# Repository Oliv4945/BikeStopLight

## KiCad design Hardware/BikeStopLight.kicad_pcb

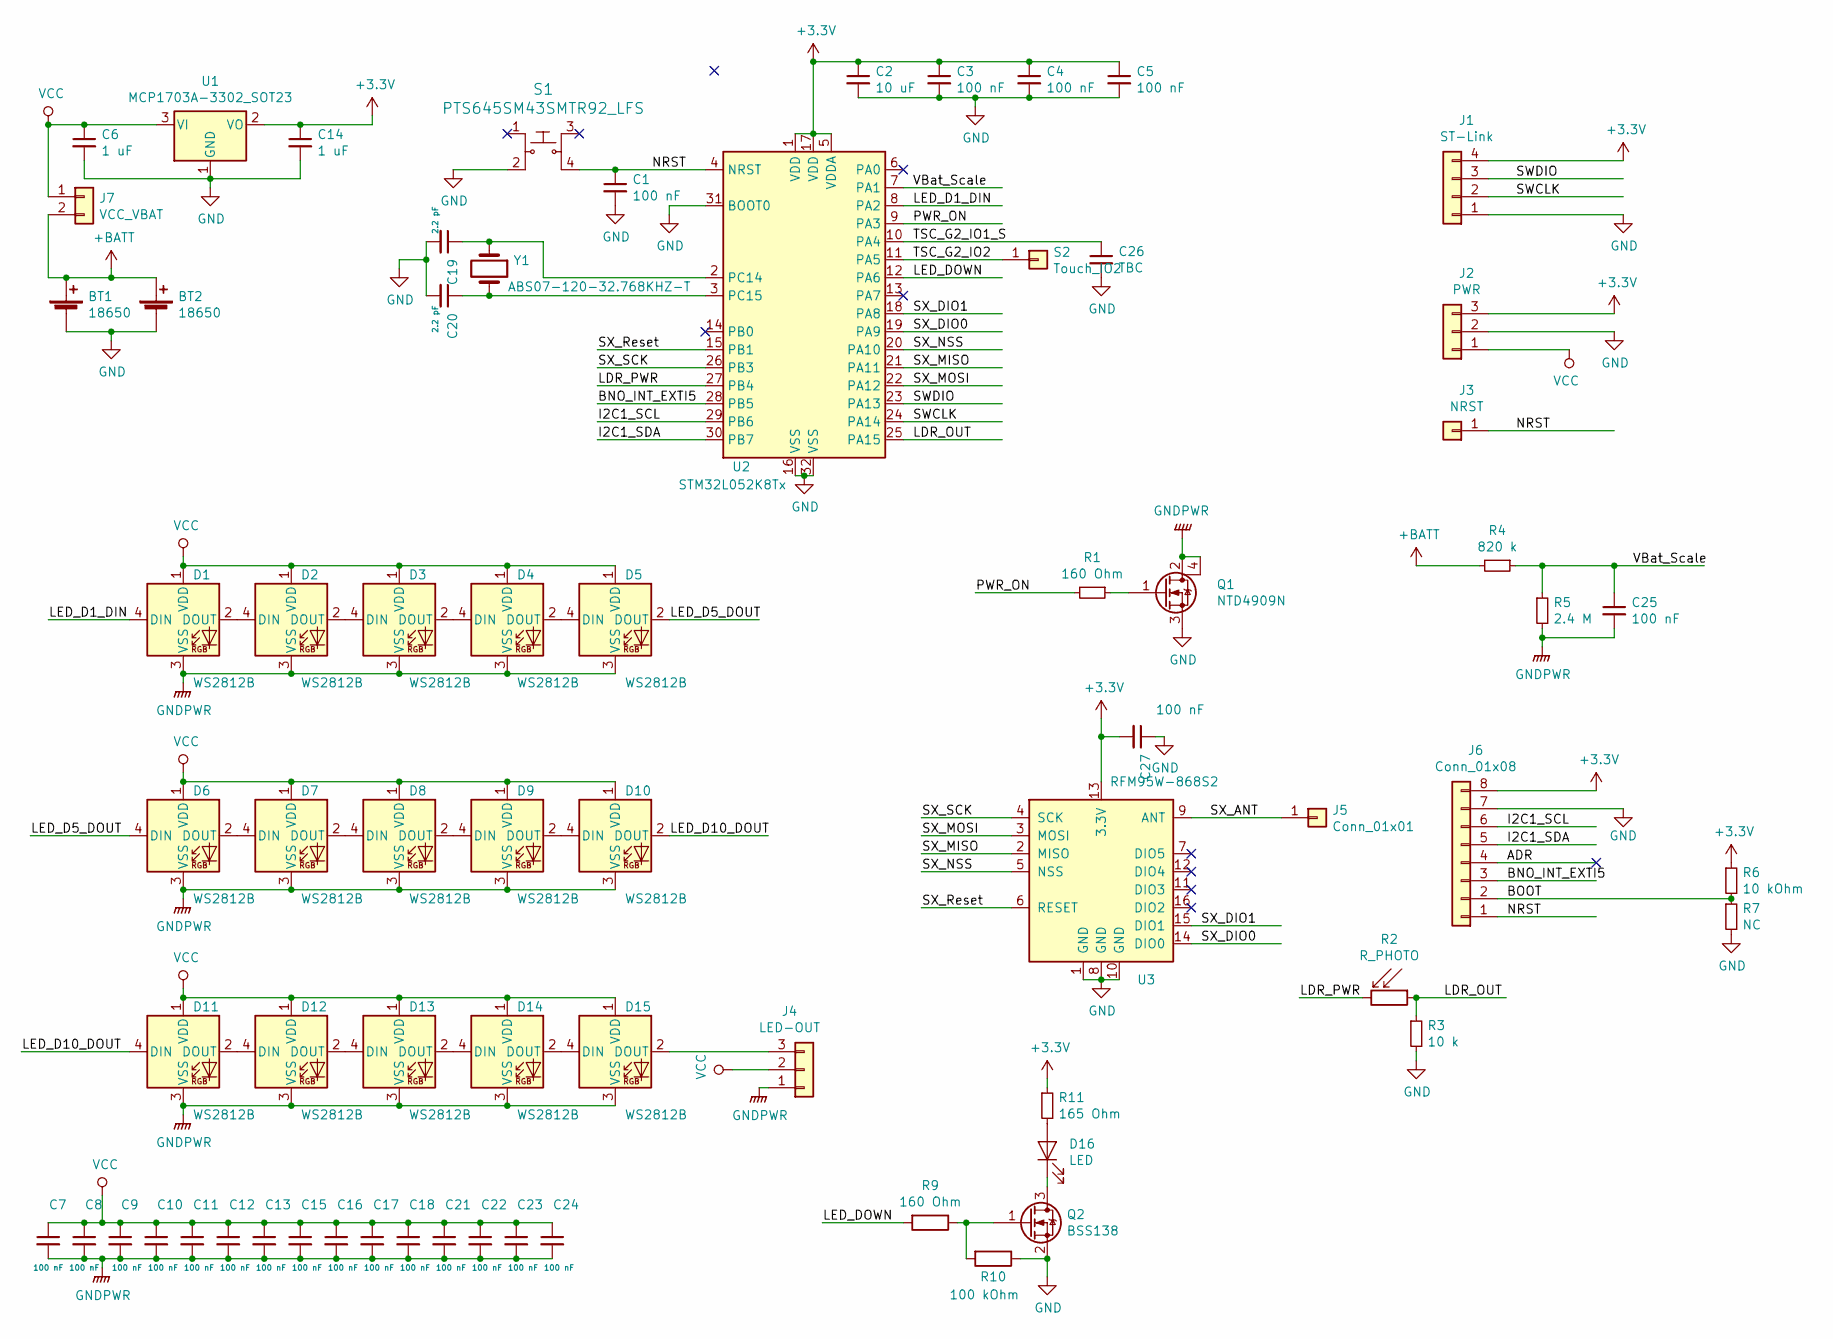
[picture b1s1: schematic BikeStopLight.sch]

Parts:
BT1, BT2: 18650; BatteryHolder_MPD_BH-18650-PC2
C1, C3, C4, C5, C7, C8, C9, C10, C11, C12, C13, C15, C16, C17, C18, C21, C22, C23, C24, C25, C27: 100 nF; C_0805_2012Metric
C2: 10 uF; C_0805_2012Metric
C6, C14: 1 uF; C_0805_2012Metric
C19, C20: 2.2 pF; C_0805_2012Metric
C26: TBC; C_0805_2012Metric
D1, D2, D3, D4, D5, D6, D7, D8, D9, D10, D11, D12, D13, D14, D15: WS2812B; LED_WS2812B_PLCC4_5.0x5.0mm_P3.2mm
D16: LED; LED_D5.0mm
J1: ST-Link; PinHeader_1x04_P2.54mm_Vertical
J2: PWR; PinHeader_1x03_P2.54mm_Vertical
J3: NRST; PinHeader_1x01_P2.54mm_Vertical
J4: LED-OUT; PinHeader_1x03_P2.54mm_Vertical
J5: Conn_01x01; PinHeader_1x01_P2.54mm_Vertical
J6: Conn_01x08; PinHeader_1x08_P2.54mm_Vertical
J7: VCC_VBAT; PinHeader_1x02_P2.54mm_Vertical
Q1: NTD4909N; DPAK229P990X238-3N
Q2: BSS138; SOT-23
R1, R9: 160 Ohm; R_0805_2012Metric
R2: R_PHOTO; R_LDR_4.9x4.2mm_P2.54mm_Vertical
R3: 10 k; R_0805_2012Metric
R4: 820 k; R_0805_2012Metric
R5: 2.4 M; R_0805_2012Metric
R6: 10 kOhm; R_0805_2012Metric
R7: NC; R_0805_2012Metric
R10: 100 kOhm; R_0805_2012Metric
R11: 165 Ohm; R_0805_2012Metric
S1: PTS645SM43SMTR92_LFS; Switch_Tactile_SMD_6x6mm_PTS645; MPN PTS645SM43SMTR92 LFS; Digi-Key_PN CKN9112CT-ND
S2: Touch_IO2; Capacitive_Touch_6_mm
U1: MCP1703A-3302_SOT23; SOT-23
U2: STM32L052K8Tx; LQFP-32_7x7mm_P0.8mm
U3: RFM95W-868S2; HOPERF_RFM9XW_SMD
Y1: ABS07-120-32.768KHZ-T; XTAL_ABS07-120-32.768KHZ-T

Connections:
+3V3: C2.1, C3.1, C4.1, C5.1, C14.1, C27.2, J1.4, J2.3, J6.8, R6.1, R11.1, U1.2 (VO), U2.1 (VDD), U2.5 (VDDA), U2.17 (VDD), U3.13 (3.3V)
+BATT: BT1.1 (+), BT2.1 (+), J7.2, R4.2
/ADR: J6.4
/BNO_INT_EXTI5: J6.3, U2.28 (PB5)
/BOOT: J6.2, R6.2, R7.1
/I2C1_SCL: J6.6, U2.29 (PB6)
/I2C1_SDA: J6.5, U2.30 (PB7)
/LDR_OUT: R2.1, R3.1, U2.25 (PA15)
/LDR_PWR: R2.2, U2.27 (PB4)
/LED_D1_DIN: D1.4 (DIN), U2.8 (PA2)
/LED_D5_DOUT: D5.2 (DOUT), D6.4 (DIN)
/LED_D10_DOUT: D10.2 (DOUT), D11.4 (DIN)
/LED_DOWN: R9.2, U2.12 (PA6)
/NRST: C1.1, J3.1, J6.1, S1.4, U2.4 (NRST)
/PWR_ON: R1.2, U2.9 (PA3)
/SWCLK: J1.2, U2.24 (PA14)
/SWDIO: J1.3, U2.23 (PA13)
/SX_ANT: J5.1, U3.9 (ANT)
/SX_DIO0: U2.19 (PA9), U3.14 (DIO0)
/SX_DIO1: U2.18 (PA8), U3.15 (DIO1)
/SX_MISO: U2.21 (PA11), U3.2 (MISO)
/SX_MOSI: U2.22 (PA12), U3.3 (MOSI)
/SX_NSS: U2.20 (PA10), U3.5 (NSS)
/SX_Reset: U2.15 (PB1), U3.6 (RESET)
/SX_SCK: U2.26 (PB3), U3.4 (SCK)
/TSC_G2_IO1_S: C26.1, U2.10 (PA4)
/TSC_G2_IO2: S2.1, U2.11 (PA5)
/VBat_Scale: C25.1, R4.1, R5.1, U2.7 (PA1)
GND: BT1.2 (-), BT2.2 (-), C1.2, C2.2, C3.2, C4.2, C5.2, C6.2, C14.2, C19.2, C20.2, C26.2, C27.1, J1.1, J2.2, J6.7, Q1.3 (S), Q2.2 (S), R3.2, R7.2, R10.1, S1.2, U1.1 (GND), U2.16 (VSS), U2.31 (BOOT0), U2.32 (VSS), U3.1 (GND), U3.8 (GND), U3.10 (GND)
GNDPWR: C7.2, C8.2, C9.2, C10.2, C11.2, C12.2, C13.2, C15.2, C16.2, C17.2, C18.2, C21.2, C22.2, C23.2, C24.2, C25.2, D1.3 (VSS), D2.3 (VSS), D3.3 (VSS), D4.3 (VSS), D5.3 (VSS), D6.3 (VSS), D7.3 (VSS), D8.3 (VSS), D9.3 (VSS), D10.3 (VSS), D11.3 (VSS), D12.3 (VSS), D13.3 (VSS), D14.3 (VSS), D15.3 (VSS), J4.1, Q1.2 (D), Q1.4 (D), R5.2
unnamed: C19.1, U2.2 (PC14), Y1.1
unnamed: C20.1, U2.3 (PC15), Y1.2
unnamed: D1.2 (DOUT), D2.4 (DIN)
unnamed: D2.2 (DOUT), D3.4 (DIN)
unnamed: D3.2 (DOUT), D4.4 (DIN)
unnamed: D4.2 (DOUT), D5.4 (DIN)
unnamed: D6.2 (DOUT), D7.4 (DIN)
unnamed: D7.2 (DOUT), D8.4 (DIN)
unnamed: D8.2 (DOUT), D9.4 (DIN)
unnamed: D9.2 (DOUT), D10.4 (DIN)
unnamed: D11.2 (DOUT), D12.4 (DIN)
unnamed: D12.2 (DOUT), D13.4 (DIN)
unnamed: D13.2 (DOUT), D14.4 (DIN)
unnamed: D14.2 (DOUT), D15.4 (DIN)
unnamed: D15.2 (DOUT), J4.3
unnamed: D16.1 (K), Q2.3 (D)
unnamed: D16.2 (A), R11.2
unnamed: Q1.1 (G), R1.1
unnamed: Q2.1 (G), R9.1, R10.2
VCC: C6.1, C7.1, C8.1, C9.1, C10.1, C11.1, C12.1, C13.1, C15.1, C16.1, C17.1, C18.1, C21.1, C22.1, C23.1, C24.1, D1.1 (VDD), D2.1 (VDD), D3.1 (VDD), D4.1 (VDD), D5.1 (VDD), D6.1 (VDD), D7.1 (VDD), D8.1 (VDD), D9.1 (VDD), D10.1 (VDD), D11.1 (VDD), D12.1 (VDD), D13.1 (VDD), D14.1 (VDD), D15.1 (VDD), J2.1, J4.2, J7.1, U1.3 (VI)

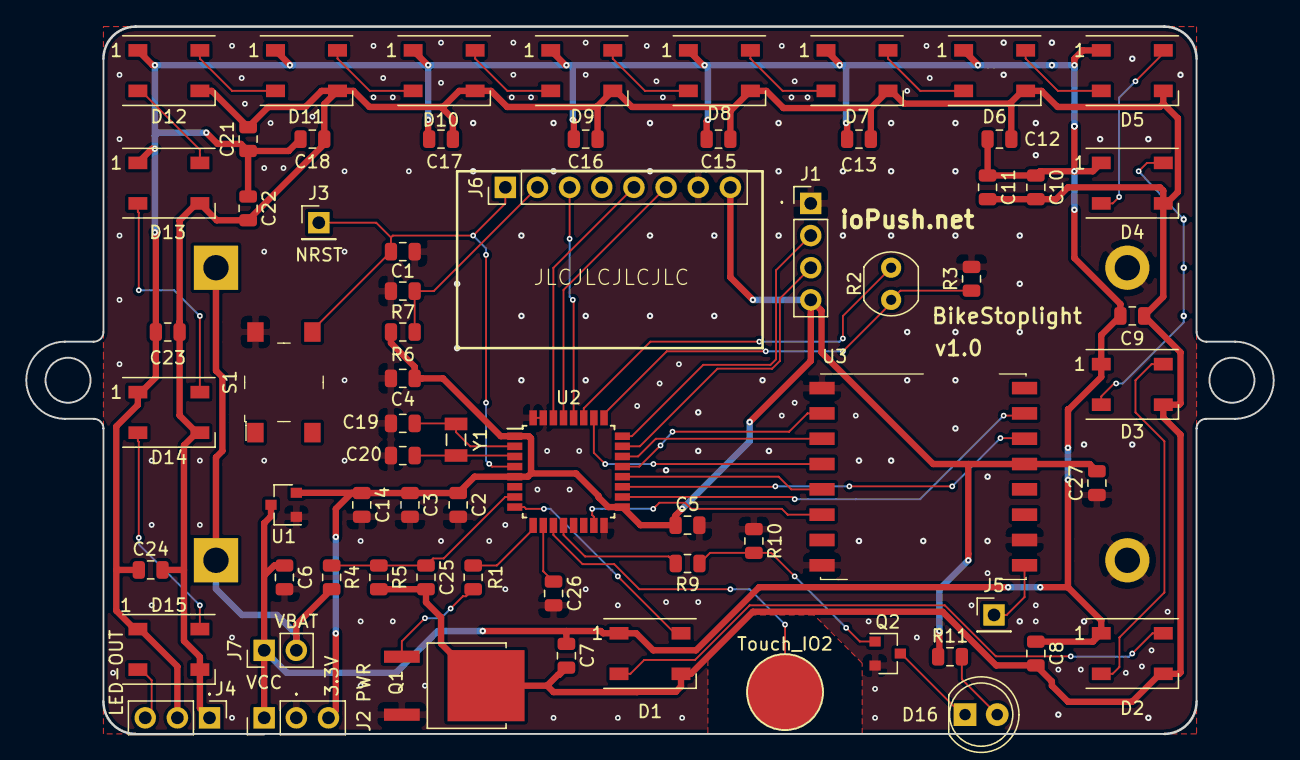
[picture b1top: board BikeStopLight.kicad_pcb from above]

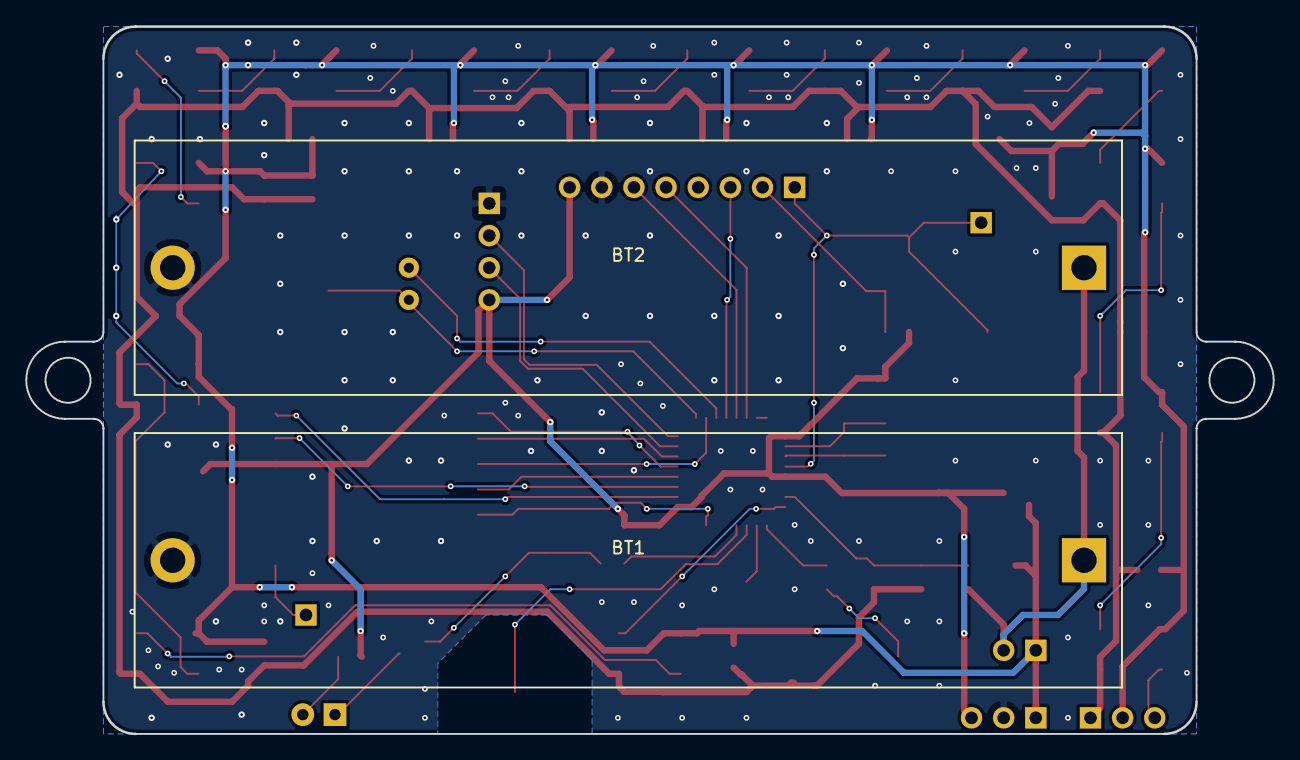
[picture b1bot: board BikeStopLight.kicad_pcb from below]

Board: 2 copper layers, 98.5 x 55.9 mm, 70 parts (2 on the bottom side), 49 nets.

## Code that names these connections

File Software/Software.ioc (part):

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Mcu.Name=STM32L052K(6-8)Tx
Mcu.Package=LQFP32
Mcu.UserName=STM32L052K8Tx
PA0.Signal=GPIO_Analog
PA1.GPIOParameters=GPIO_Label
PA1.GPIO_Label=VBAT_SCALE
PA1.Signal=SharedAnalog_PA1
PA10.GPIOParameters=GPIO_Label
PA10.GPIO_Label=SX_NSS
PA10.Signal=GPIO_Output
PA11.Mode=Full_Duplex_Master
PA11.Signal=SPI1_MISO
PA12.Mode=Full_Duplex_Master
PA12.Signal=SPI1_MOSI
PA13.Mode=Serial_Wire
PA13.Signal=SYS_SWDIO
PA14.Mode=Serial_Wire
PA14.Signal=SYS_SWCLK
PA15.Signal=GPIO_Analog
PA2.GPIOParameters=GPIO_PuPd,GPIO_Label
PA2.GPIO_Label=WS2812_DIN
PA2.GPIO_PuPd=GPIO_NOPULL
PA2.Signal=S_TIM2_CH3
PA3.GPIOParameters=GPIO_Label
PA3.GPIO_Label=WS2812_PWR_ON
PA3.Signal=GPIO_Output
PA4.GPIOParameters=GPIO_Label
PA4.GPIO_Label=TSC_G2_SAMPLING
PA4.Mode=G2_IO1-Sampling
PA4.Signal=TSC_G2_IO1
PA5.GPIOParameters=GPIO_Label
PA5.GPIO_Label=TSC_G2_IN
PA5.Mode=G2_IO2-Channel
PA5.Signal=TSC_G2_IO2
PA6.GPIOParameters=GPIO_Label
PA6.GPIO_Label=LED_DOWN
PA6.Signal=GPIO_Output
PA7.Signal=GPIO_Analog
PA8.GPIOParameters=GPIO_Label
PA8.GPIO_Label=SX_DIO0_EXTI8
PA8.Signal=GPXTI8
PA9.GPIOParameters=GPIO_Label
PA9.GPIO_Label=SX_DIO0_EXTI9
PA9.Signal=GPXTI9
PB0.GPIOParameters=GPIO_Label
PB0.GPIO_Label=LDR_IN
PB0.Signal=SharedAnalog_PB0
PB1.GPIOParameters=GPIO_Label
PB1.GPIO_Label=SX_RESET
PB1.Signal=GPIO_Output
PB3.Mode=Full_Duplex_Master
PB3.Signal=SPI1_SCK
PB4.GPIOParameters=GPIO_Label
PB4.GPIO_Label=LDR_PWR
PB4.Signal=GPIO_Output
PB5.GPIOParameters=GPIO_Label
PB5.GPIO_Label=BNO_INT_EXTI5
PB5.Signal=GPXTI5
PB6.Mode=I2C
PB6.Signal=I2C1_SCL
PB7.Mode=I2C
PB7.Signal=I2C1_SDA
RCC.SYSCLKFreq_VALUE=16000000
RCC.SYSCLKSource=RCC_SYSCLKSOURCE_HSI
board=custom

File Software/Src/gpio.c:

/**
  ******************************************************************************
  * File Name          : gpio.c
  * Description        : This file provides code for the configuration
  *                      of all used GPIO pins.
  ******************************************************************************
  * @attention
  *
  * <h2><center>&copy; Copyright (c) 2020 STMicroelectronics.
  * All rights reserved.</center></h2>
  *
  * This software component is licensed by ST under Ultimate Liberty license
  * SLA0044, the "License"; You may not use this file except in compliance with
  * the License. You may obtain a copy of the License at:
  *                             www.st.com/SLA0044
  *
  ******************************************************************************
  */

/* Includes ------------------------------------------------------------------*/
#include "gpio.h"
/* USER CODE BEGIN 0 */

/* USER CODE END 0 */

/*----------------------------------------------------------------------------*/
/* Configure GPIO                                                             */
/*----------------------------------------------------------------------------*/
/* USER CODE BEGIN 1 */

/* USER CODE END 1 */

/** Configure pins
     PA1   ------> SharedAnalog_PA1
     PB0   ------> SharedAnalog_PB0
*/
void MX_GPIO_Init(void)
{

  GPIO_InitTypeDef GPIO_InitStruct = {0};

  /* GPIO Ports Clock Enable */
  __HAL_RCC_GPIOC_CLK_ENABLE();
  __HAL_RCC_GPIOA_CLK_ENABLE();
  __HAL_RCC_GPIOB_CLK_ENABLE();

  /*Configure GPIO pin Output Level */
  HAL_GPIO_WritePin(GPIOA, WS2812_PWR_ON_Pin|LED_DOWN_Pin|SX_NSS_Pin, GPIO_PIN_RESET);

  /*Configure GPIO pin Output Level */
  HAL_GPIO_WritePin(GPIOB, SX_RESET_Pin|LDR_PWR_Pin, GPIO_PIN_RESET);

  /*Configure GPIO pins : PC14 PC15 */
  GPIO_InitStruct.Pin = GPIO_PIN_14|GPIO_PIN_15;
  GPIO_InitStruct.Mode = GPIO_MODE_ANALOG;
  GPIO_InitStruct.Pull = GPIO_NOPULL;
  HAL_GPIO_Init(GPIOC, &GPIO_InitStruct);

  /*Configure GPIO pins : PA0 PAPin PA7 PA15 */
  GPIO_InitStruct.Pin = GPIO_PIN_0|VBAT_SCALE_Pin|GPIO_PIN_7|GPIO_PIN_15;
  GPIO_InitStruct.Mode = GPIO_MODE_ANALOG;
  GPIO_InitStruct.Pull = GPIO_NOPULL;
  HAL_GPIO_Init(GPIOA, &GPIO_InitStruct);

  /*Configure GPIO pins : PAPin PAPin PAPin */
  GPIO_InitStruct.Pin = WS2812_PWR_ON_Pin|LED_DOWN_Pin|SX_NSS_Pin;
  GPIO_InitStruct.Mode = GPIO_MODE_OUTPUT_PP;
  GPIO_InitStruct.Pull = GPIO_NOPULL;
  GPIO_InitStruct.Speed = GPIO_SPEED_FREQ_LOW;
  HAL_GPIO_Init(GPIOA, &GPIO_InitStruct);

  /*Configure GPIO pin : PtPin */
  GPIO_InitStruct.Pin = LDR_IN_Pin;
  GPIO_InitStruct.Mode = GPIO_MODE_ANALOG;
  GPIO_InitStruct.Pull = GPIO_NOPULL;
  HAL_GPIO_Init(LDR_IN_GPIO_Port, &GPIO_InitStruct);

  /*Configure GPIO pins : PBPin PBPin */
  GPIO_InitStruct.Pin = SX_RESET_Pin|LDR_PWR_Pin;
  GPIO_InitStruct.Mode = GPIO_MODE_OUTPUT_PP;
  GPIO_InitStruct.Pull = GPIO_NOPULL;
  GPIO_InitStruct.Speed = GPIO_SPEED_FREQ_LOW;
  HAL_GPIO_Init(GPIOB, &GPIO_InitStruct);

  /*Configure GPIO pins : PAPin PAPin */
  GPIO_InitStruct.Pin = SX_DIO0_EXTI8_Pin|SX_DIO0_EXTI9_Pin;
  GPIO_InitStruct.Mode = GPIO_MODE_IT_RISING;
  GPIO_InitStruct.Pull = GPIO_NOPULL;
  HAL_GPIO_Init(GPIOA, &GPIO_InitStruct);

  /*Configure GPIO pin : PtPin */
  GPIO_InitStruct.Pin = BNO_INT_EXTI5_Pin;
  GPIO_InitStruct.Mode = GPIO_MODE_IT_RISING;
  GPIO_InitStruct.Pull = GPIO_NOPULL;
  HAL_GPIO_Init(BNO_INT_EXTI5_GPIO_Port, &GPIO_InitStruct);

  /* EXTI interrupt init*/
  HAL_NVIC_SetPriority(EXTI4_15_IRQn, 0, 0);
  HAL_NVIC_EnableIRQ(EXTI4_15_IRQn);

}

/* USER CODE BEGIN 2 */

/* USER CODE END 2 */

/************************ (C) COPYRIGHT STMicroelectronics *****END OF FILE****/

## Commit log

2019-05-07 Init
2019-05-18 WIP - Started layout
2019-05-18 Untrack .bak files
2019-05-18 Add .gitignore
2019-05-18 WIP - Routed
2019-05-18 WIP - Add touch & GND via
2019-06-30 WIP - Add red light
2019-06-30 BSS138 mosfet doc
2019-07-25 Add reset connector
2019-07-25 Change fixing holes, silkscreen changes
2019-07-25 Add connector for Vbat to Vcc
2019-07-25 Add JLPCB prod text placeholder
2019-08-11 Add Eagle lib
2019-09-29 Add doc files
2019-10-14 Init software & VSCode
2019-10-14 Update BN0 board docs
2019-10-26 Add LDR
2019-11-07 Add STM32 GPIO low power AN
2019-11-07 Add vscode files
2020-01-08 Update Cube libs and disable external xtal
2020-01-08 BNO in low power mode
2020-12-02 Switch BNO parameters from constants to defines
2020-12-03 Working interrupts
2020-12-03 Move BNO init to its own function
2020-12-03 Disable I2C in stop mode
2020-12-06 Move stop move entry to its own function
2020-12-06 Activate LSI and use it for LPTIM1
2020-12-06 Update CubeMX libraries
